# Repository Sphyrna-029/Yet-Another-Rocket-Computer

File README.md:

# Yet-Another-Rocket-Computer
YARC (Yet Another Rocket Comptuer). Rocket flight computers are all the craze nowa-days. This is my attempt at one.

##### Features
 - 3-axis gyroscope and a 3-axis accelerometer (MPU6050)
 - GPS (LC86G with built in patch)
 - Telemetry (1 Watt Ebyte E22 Lora Module)
 - Total footprint is 35mm x 90mm
<br/>
<br/>
Firmware will track flight events (launch, apogee, landing), altitude, location, and attitude. In addition to aiding in post flight recovery. 
<br/>
<br/>
<br/>

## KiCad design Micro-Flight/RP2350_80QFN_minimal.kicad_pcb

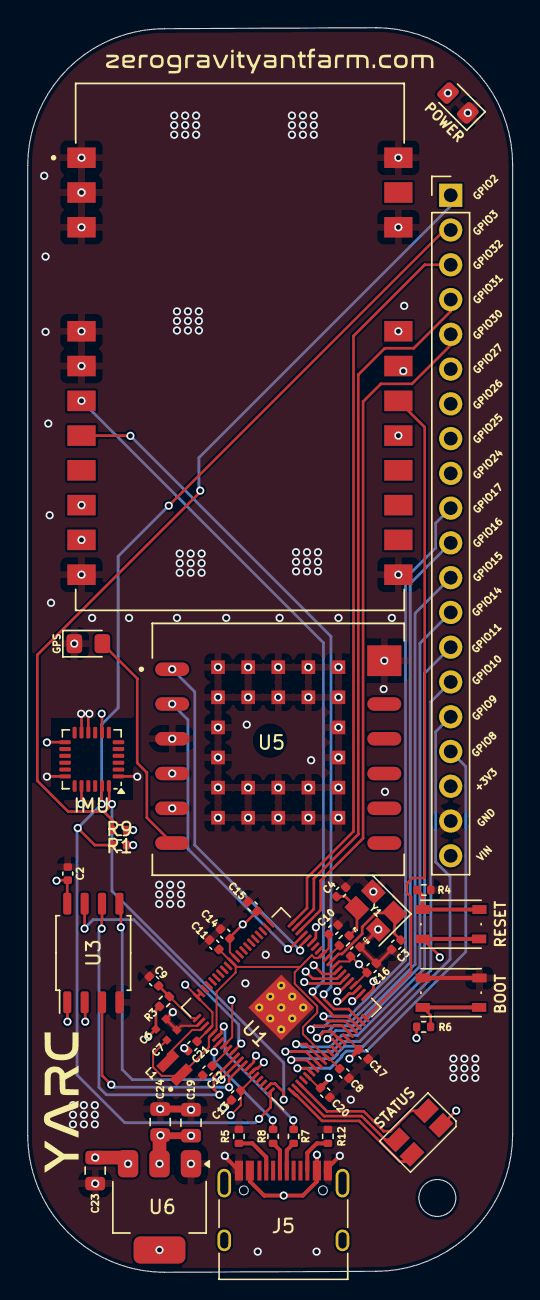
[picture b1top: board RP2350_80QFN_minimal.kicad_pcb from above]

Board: 4 copper layers, 35.4 x 90.9 mm, 47 parts (0 on the bottom side), 53 nets.

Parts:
BOOT: SW_Push; SW_Push_1P1T_NO_Vertical_Wuerth_434133025816
C2, C8, C11, C12, C13, C14, C15, C16, C17, C18, C20, C21: 100n; C_0402_1005Metric
C3, C4: 15p; C_0402_1005Metric
C6, C7: 4.7u; C_0402_1005Metric_small_pads
C9, C10: 4.7u; C_0402_1005Metric
C19, C23, C24: 10u; C_0805_2012Metric
GPS: LED; LED_0805_2012Metric_Pad1.15x1.40mm_HandSolder
H3: MountingHole; MountingHole_2.7mm_M2.5
IMU: MPU-6050; InvenSense_QFN-24_4x4mm_P0.5mm
J2: Conn_01x20; PinHeader_1x20_P2.54mm_Vertical
J5: USB_C_Receptacle_USB2.0_14P; USB_C_Receptacle_HRO_TYPE-C-31-M-12
L1: 3.3u; L_pol_2016
POWER: LED; LED_0805_2012Metric_Pad1.15x1.40mm_HandSolder
R1, R9: 4.7k; R_0402_1005Metric
R2, R4, R6: 1k; R_0402_1005Metric
R3: 33; R_0402_1005Metric
R5, R12: 5.1k; R_0402_1005Metric
R7, R8: 27; R_0402_1005Metric
RESET: SW_Push; SW_Push_1P1T_NO_Vertical_Wuerth_434133025816
STATUS: LED_ARGB; LED_Avago_PLCC4_3.2x2.8mm_CW
U1: RP2350_80QFN; RP2350-QFN-80-1EP_10x10_P0.4mm_EP3.4x3.4mm_ThermalVias
U2: E22-900M30S; XCVR_E22-900M30S
U3: W25Q128JVS; SOIC-8_5.23x5.23mm_P1.27mm
U5: LC86G; XCVR_LC86G
U6: NCP1117-3.3_SOT223; SOT-223-3_TabPin2
Y1: ABM8-272-T3; Crystal_SMD_3225-4Pin_3.2x2.5mm

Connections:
+1V1: C7.1, C8.1, C10.1, C11.1, L1.1, U1.10 (DVDD), U1.32 (DVDD), U1.51 (DVDD), U1.65 (VREG_FB)
+3V3: C2.1, C6.1, C12.1, C13.1, C14.1, C15.1, C16.1, C17.1, C18.1, C19.1, C20.1, C21.1, C24.1, IMU.8 (VLOGIC), IMU.13 (VDD), J2.18, POWER.2 (A), R1.1, R3.1, R9.2, STATUS.1 (A), U1.5 (IOVDD), U1.15 (IOVDD), U1.24 (IOVDD), U1.29 (IOVDD), U1.41 (IOVDD), U1.50 (IOVDD), U1.59 (ADC_AVDD), U1.60 (IOVDD), U1.64 (VREG_VIN), U1.68 (USB_OTP_VDD), U1.69 (QSPI_IOVDD), U1.76 (IOVDD), U2.9 (VCC), U2.10 (VCC), U3.8 (VCC), U5.4 (VCC), U5.5 (V_BCKP), U6.2 (VO)
/FLASH_SS: R6.1, U1.75 (QSPI_SS), U3.1 (~CS)
/GPIO2: IMU.24 (SDA), J2.1, R1.2, U1.79 (GPIO2)
/GPIO3: IMU.23 (SCL), J2.2, R9.1, U1.80 (GPIO3)
/GPIO4: STATUS.2 (RK), U1.1 (GPIO4)
/GPIO5: STATUS.3 (GK), U1.2 (GPIO5)
/GPIO6: STATUS.4 (BK), U1.3 (GPIO6)
/GPIO8: J2.17, U1.6 (GPIO8)
/GPIO9: J2.16, U1.7 (GPIO9)
/GPIO10: J2.15, U1.8 (GPIO10)
/GPIO11: J2.14, U1.9 (GPIO11)
/GPIO14: J2.13, U1.13 (GPIO14)
/GPIO15: J2.12, U1.14 (GPIO15)
/GPIO16: J2.11, U1.16 (GPIO16)
/GPIO17: J2.10, U1.17 (GPIO17)
/GPIO18: U1.18 (GPIO18), U2.6 (RXEN)
/GPIO19: U1.19 (GPIO19), U2.7 (TXEN)
/GPIO20: U1.20 (GPIO20), U2.17 (MOSI)
/GPIO21: U1.21 (GPIO21), U2.19 (NSS)
/GPIO22: U1.22 (GPIO22), U2.18 (SCK)
/GPIO23: U1.23 (GPIO23), U2.16 (MISO)
/GPIO24: J2.9, U1.25 (GPIO24)
/GPIO25: J2.8, U1.26 (GPIO25)
/GPIO26: J2.7, U1.27 (GPIO26)
/GPIO27: J2.6, U1.28 (GPIO27)
/GPIO28: U1.36 (GPIO28), U5.1 (RXD)
/GPIO29: U1.37 (GPIO29), U5.2 (TXD)
/GPIO30: J2.5, U1.38 (GPIO30)
/GPIO31: J2.4, U1.39 (GPIO31)
/GPIO32: J2.3, U1.40 (GPIO32)
/QSPI_SCLK: U1.71 (QSPI_SCLK), U3.6 (CLK)
/QSPI_SD0: U1.72 (QSPI_SD0), U3.5 (DI(IO0))
/QSPI_SD1: U1.74 (QSPI_SD1), U3.2 (DO(IO1))
/QSPI_SD2: U1.73 (QSPI_SD2), U3.3 (IO2)
/QSPI_SD3: U1.70 (QSPI_SD3), U3.7 (IO3)
/RUN: RESET.2, U1.35 (RUN)
/USB_D+: J5.A6 (D+), R7.1
/USB_D-: J5.A7 (D-), R8.1
/VREG_AVDD: C9.1, R3.2, U1.61 (VREG_AVDD)
/VREG_LX: L1.2, U1.63 (VREG_LX)
/XIN: C3.1, U1.30 (XIN), Y1.1
/XOUT: R2.1, U1.31 (XOUT)
/~USB_BOOT: BOOT.2, R6.2
GND: BOOT.1, C2.2, C3.2, C4.2, C6.2, C7.2, C8.2, C9.2, C10.2, C11.2, C12.2, C13.2, C14.2, C15.2, C16.2, C17.2, C18.2, C19.2, C20.2, C21.2, C23.2, C24.2, GPS.1 (K), IMU.1 (CLKIN), IMU.10 (REGOUT), IMU.11 (FSYNC), IMU.18 (GND), IMU.20 (CPOUT), J2.19, J5.A1 (GND), J5.A12 (GND), J5.B1 (GND), J5.B12 (GND), POWER.1 (K), R4.2, R5.1, R12.1, U1.62 (VREG_PGND), U1.81 (GND), U2.1 (GND), U2.2 (GND), U2.3 (GND), U2.4 (GND), U2.5 (GND), U2.11 (GND), U2.12 (GND), U2.20 (GND), U2.22 (GND), U3.4 (GND), U5.3 (GND), U5.12 (GND), U5.13 (GND), U5.14 (GND), U5.15 (GND), U5.16 (GND), U5.17 (GND), U5.18 (GND), U5.19 (GND), U5.20 (GND), U5.21 (GND), U5.22 (GND), U5.23 (GND), U5.24 (GND), U5.25 (GND), U5.26 (GND), U5.27 (GND), U5.28 (GND), U5.29 (GND), U5.30 (GND), U5.31 (GND), U5.32 (GND), U5.33 (GND), U5.34 (GND), U5.35 (GND), U5.36 (GND), U6.1 (GND), Y1.2, Y1.4
unnamed: C4.1, R2.2, Y1.3
unnamed: GPS.2 (A), U5.6 (1PPS)
unnamed: J5.A5 (CC1), R5.2
unnamed: J5.B5 (CC2), R12.2
unnamed: R4.1, RESET.1
unnamed: R8.2, U1.66 (USB_DM)
unnamed: R7.2, U1.67 (USB_DP)
VBUS: C23.1, J2.20, J5.A4 (VBUS), J5.A9 (VBUS), J5.B4 (VBUS), J5.B9 (VBUS), U6.3 (VI)

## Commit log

2025-05-11 Rev A
2025-05-27 REV B
